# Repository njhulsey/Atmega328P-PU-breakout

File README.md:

# Atmega328P-PU-breakout
Breakout Chip for the Atmega328P-PU

This is a breakout board for the Atmega328 chip with an external 16 Mhz crystal. You can plug a 9v battery into it as well. It also includes a power switch and a few LEDS. You can program the chip using the ICSP pins and using a programmer (like the USBTinyISP). This was my attempt of recreating my own Arduino Uno. 

Includes:
  - Pinheaders
  - 16Mhz Crystal
  - 5V regulator 
  - Power switch
  - ICSP pins
 
What I learned:
  - How to use a crystal
  - Programming/working with Atmega328P-PU and Atmega238P

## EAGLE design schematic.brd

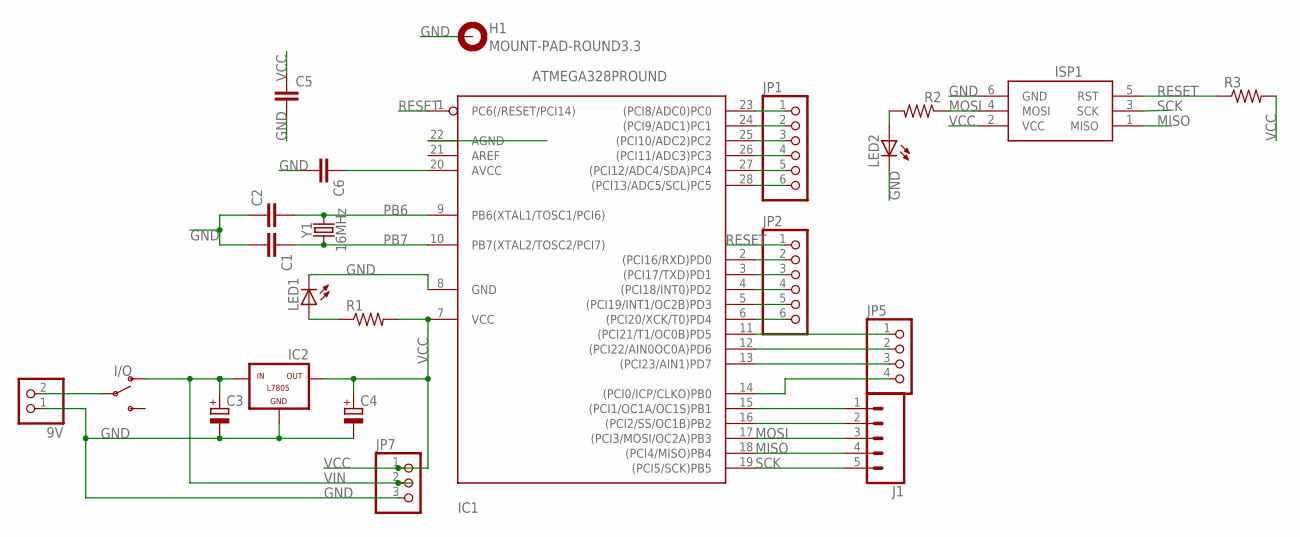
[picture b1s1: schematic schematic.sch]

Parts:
9V: PINHD-1X2M; 1X02M
C1, C2: C5/5; C5B5
C3, C4: CPOL-EUB45181A; B45181A
C5, C6: C-EU025-025X050; C025-025X050
H1: MOUNT-PAD-ROUND3.3; 3,3-PAD
I/O: SWITCH-SPDT-PTH-11.6X4.0MM; SWITCH_SPDT_PTH_11.6X4.0MM
IC1: ATMEGA328PROUND; DIL28-3-ROUND
IC2: L7805; 78XXL
ISP1: AVRISP-6; AVRISP
J1: CONN_05; 1X05
JP1, JP2: PINHD-1X6; 1X06
JP5: PINHD-1X4; 1X04
JP7: PINHD-1X3; 1X03
LED1, LED2: LED3MM
R1, R2, R3: R-US_0207/10; 0207/10
Y1: 16MHz; HC49US

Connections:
GND: 9V.1, C1.2, C2.1, C3.-, C4.-, C5.2, C6.2, H1.B3,3, IC1.8 (GND), IC1.22 (AGND), IC2.GND, ISP1.6 (GND), JP7.3, LED1.K (C), LED2.K (C)
MISO: IC1.18 ((PCI4/MISO)PB4), ISP1.1 (MISO), J1.4
MOSI: IC1.17 ((PCI3/MOSI/OC2A)PB3), ISP1.4 (MOSI), J1.3, R2.1
unnamed: 9V.2, I/O.2
unnamed: LED1.A, R1.1
unnamed: IC1.28 ((PCI13/ADC5/SCL)PC5), JP1.6
unnamed: IC1.27 ((PCI12/ADC4/SDA)PC4), JP1.5
unnamed: IC1.16 ((PCI2/SS/OC1B)PB2), J1.2
unnamed: IC1.15 ((PCI1/OC1A/OC1S)PB1), J1.1
unnamed: IC1.14 ((PCI0/ICP/CLKO)PB0), JP5.4
unnamed: LED2.A, R2.2
unnamed: IC1.26 ((PCI11/ADC3)PC3), JP1.4
unnamed: IC1.25 ((PCI10/ADC2)PC2), JP1.3
unnamed: IC1.24 ((PCI9/ADC1)PC1), JP1.2
unnamed: IC1.23 ((PCI8/ADC0)PC0), JP1.1
unnamed: IC1.6 ((PCI20/XCK/T0)PD4), JP2.6
unnamed: IC1.5 ((PCI19/INT1/OC2B)PD3), JP2.5
unnamed: IC1.4 ((PCI18/INT0)PD2), JP2.4
unnamed: IC1.3 ((PCI17/TXD)PD1), JP2.3
unnamed: IC1.2 ((PCI16/RXD)PD0), JP2.2
unnamed: IC1.11 ((PCI21/T1/OC0B)PD5), JP5.1
unnamed: IC1.12 ((PCI22/AIN0OC0A)PD6), JP5.2
unnamed: IC1.13 ((PCI23/AIN1)PD7), JP5.3
unnamed: C6.1, IC1.20 (AVCC)
PB6: C2.2, IC1.9 (PB6(XTAL1/TOSC1/PCI6)), Y1.2
PB7: C1.1, IC1.10 (PB7(XTAL2/TOSC2/PCI7)), Y1.1
RESET: IC1.1 (PC6(/RESET/PCI14)), ISP1.5 (RST), JP2.1, R3.1
SCK: IC1.19 ((PCI5/SCK)PB5), ISP1.3 (SCK), J1.5
VCC: C4.+, C5.1, IC1.7 (VCC), IC2.OUT, ISP1.2 (VCC), JP7.1, R1.2, R3.2
VIN: C3.+, I/O.1 (O), IC2.IN, JP7.2

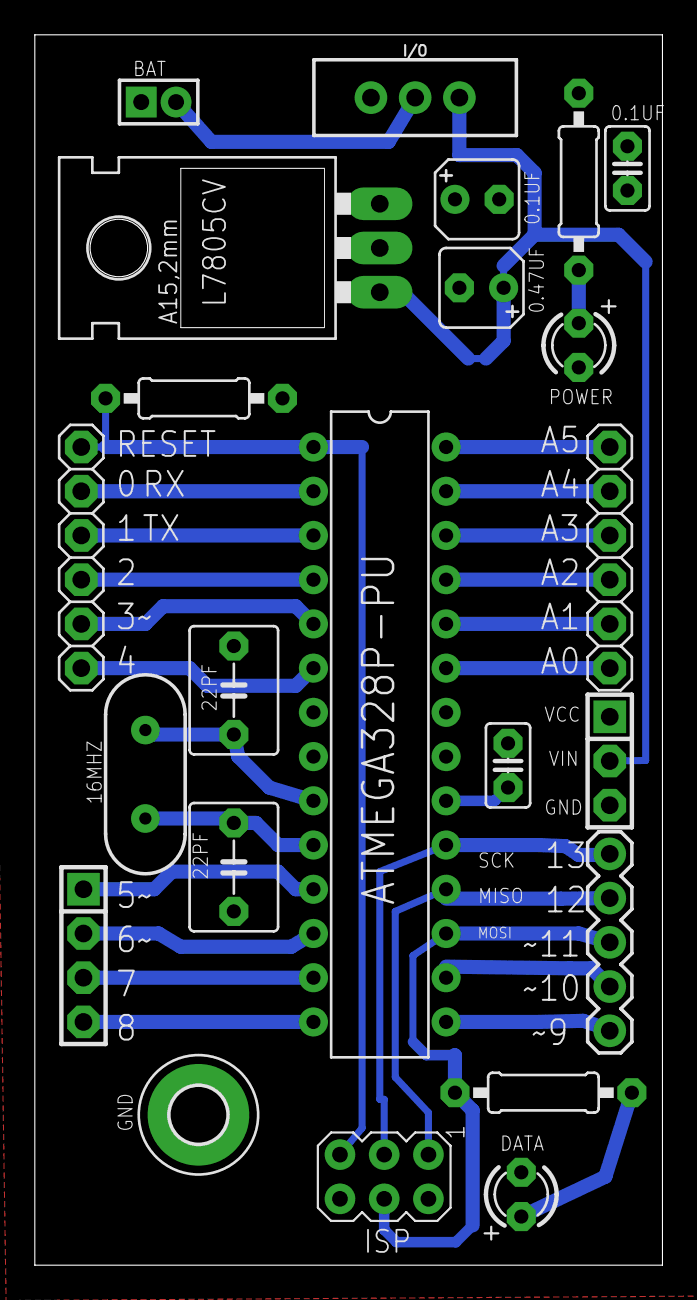
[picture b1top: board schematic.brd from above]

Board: 2 copper layers, 36.0 x 70.7 mm, 23 parts (0 on the bottom side), 30 nets.

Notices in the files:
parts and their libraries:
SparkFun-Clocks: Licensing: Creative Commons ShareAlike 4.0 International - https://creativecommons.org/licenses/by-sa/4.0
